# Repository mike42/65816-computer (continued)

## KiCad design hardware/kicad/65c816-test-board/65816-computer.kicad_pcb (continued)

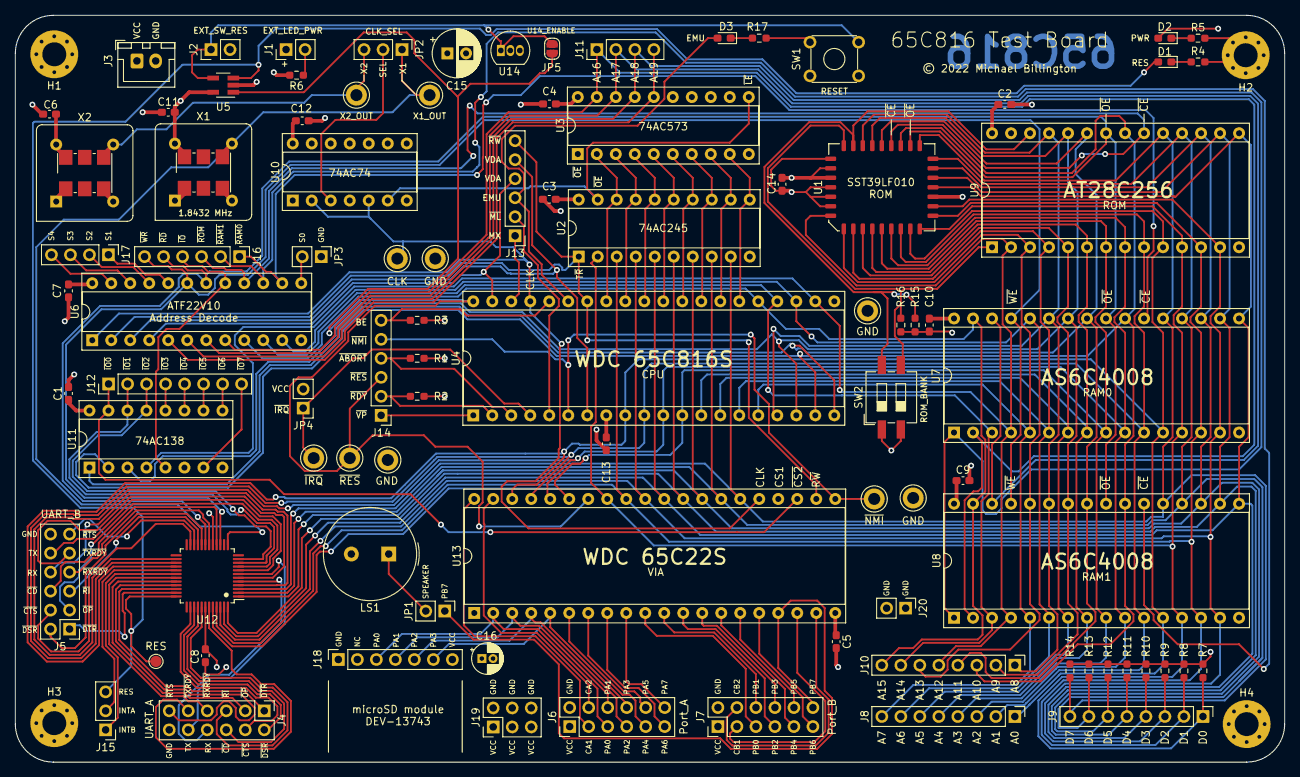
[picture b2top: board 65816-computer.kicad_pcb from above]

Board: 4 copper layers, 169.7 x 99.8 mm, 97 parts (0 on the bottom side), 128 nets.

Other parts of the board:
X1_ALT, X2_ALT: Oscillator_SMD_IDT_JU6-6_7.0x5.0mm_P2.54mm

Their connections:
+5V: X1_ALT.1, X1_ALT.6, X2_ALT.1, X2_ALT.6; also elsewhere on the board
/CPU& Bank Address Latching/CLK_UART: X1_ALT.4; also elsewhere on the board
GND: X1_ALT.3, X2_ALT.3; also elsewhere on the board
unnamed 127: X2_ALT.4; also elsewhere on the board

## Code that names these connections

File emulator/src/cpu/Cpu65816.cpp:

/*
 * This file is part of the 65816 Emulator Library.
 * Copyright (c) 2018 Francesco Rigoni.
 *
 * https://github.com/FrancescoRigoni/Lib65816
 *
 * This program is free software: you can redistribute it and/or modify
 * it under the terms of the GNU General Public License as published by
 * the Free Software Foundation, version 3.
 *
 * This program is distributed in the hope that it will be useful, but
 * WITHOUT ANY WARRANTY; without even the implied warranty of
 * MERCHANTABILITY or FITNESS FOR A PARTICULAR PURPOSE. See the GNU
 * General Public License for more details.
 *
 * You should have received a copy of the GNU General Public License
 * along with this program. If not, see <http://www.gnu.org/licenses/>.
 */

#include "Cpu65816.h"

#include <utility>

#ifdef EMU_65C02
#define LOG_TAG "Cpu65C02"
#else
#define LOG_TAG (mCpuStatus.emulationFlag() ? "Cpu6502" : "Cpu65816")
#endif

Cpu65816::Cpu65816(SystemBus &systemBus, std::shared_ptr<InterruptStatus> nmi, std::shared_ptr<InterruptStatus> irq) :
        mSystemBus(systemBus),
        mStack(&mSystemBus),
        nmi(nmi),
        irq(irq) {
    mPins.NMI = nmi->get();
}


void Cpu65816::setXL(uint8_t x) {
    mX = x;
}

void Cpu65816::setYL(uint8_t y) {
    mY = y;
}

void Cpu65816::setX(uint16_t x) {
    mX = x;
}

void Cpu65816::setY(uint16_t y) {
    mY = y;
}

void Cpu65816::setA(uint16_t a) {
    mA = a;
}

uint16_t Cpu65816::getA() {
    return mA;
}

Address Cpu65816::getProgramAddress() {
    return mProgramAddress;
}

Stack *Cpu65816::getStack() {
    return &mStack;
}

CpuStatus *Cpu65816::getCpuStatus() {
    return &mCpuStatus;
}


/**
 * Resets the cpu to its initial state.
 * */
void Cpu65816::reset() {
    setRESPin(true);
    mCpuStatus.setEmulationFlag();
    mCpuStatus.setAccumulatorWidthFlag();
    mCpuStatus.setIndexWidthFlag();
    mX &= 0xFF;
    mY &= 0xFF;
    mD = 0x0;
    mStack = Stack(&mSystemBus);
    mProgramAddress = Address(0x00, mSystemBus.readTwoBytes(Address(0x00, INTERRUPT_VECTOR_EMULATION_RESET)));
}

void Cpu65816::setRESPin(bool value) {
    if (value == false && mPins.RES == true) {
        reset();
    }
    mPins.RES = value;
}

void Cpu65816::setRDYPin(bool value) {
    mPins.RDY = value;
}

bool Cpu65816::executeNextInstruction() {
    if (mPins.RES) {
        return false;
    }
    if ((irq->get()) && (!mCpuStatus.interruptDisableFlag())) {
        /*
        The program bank register (PB, the A16-A23 part of the address bus) is pushed onto the hardware stack (65C816/65C802 only when operating in native mode).
        The most significant byte (MSB) of the program counter (PC) is pushed onto the stack.
        The least significant byte (LSB) of the program counter is pushed onto the stack.
        The status register (SR) is pushed onto the stack.
        The interrupt disable flag is set in the status register.
        PB is loaded with $00 (65C816/65C802 only when operating in native mode).
        PC is loaded from the relevant vector (see tables).
        */
        if (!mCpuStatus.emulationFlag()) {
            mStack.push8Bit(mProgramAddress.getBank());
            mStack.push16Bit(mProgramAddress.getOffset());
            mStack.push8Bit(mCpuStatus.getRegisterValue());
            mCpuStatus.setInterruptDisableFlag();
            mProgramAddress = Address(0x00, mSystemBus.readTwoBytes(Address(0x00, INTERRUPT_VECTOR_NATIVE_IRQ)));
        } else {
            mStack.push16Bit(mProgramAddress.getOffset());
            mStack.push8Bit(mCpuStatus.getRegisterValue());
            mCpuStatus.setInterruptDisableFlag();
            mProgramAddress = Address(0x00, mSystemBus.readTwoBytes(Address(0x00, INTERRUPT_VECTOR_EMULATION_BRK_IRQ)));
        }
    }
    // Edge detect NMI
    bool newNmi = nmi->get();
    if(!newNmi && mPins.NMI) {
        // De-activated
        mPins.NMI = false;
    } else if(newNmi && !mPins.NMI) {
        // Activated
        mPins.NMI = true;
        if (!mCpuStatus.emulationFlag()) {
            mStack.push8Bit(mProgramAddress.getBank());
            mStack.push16Bit(mProgramAddress.getOffset());
            mStack.push8Bit(mCpuStatus.getRegisterValue());
            mCpuStatus.setInterruptDisableFlag();
            mProgramAddress = Address(0x00, mSystemBus.readTwoBytes(Address(0x00, INTERRUPT_VECTOR_NATIVE_NMI)));
        } else {
            mStack.push16Bit(mProgramAddress.getOffset());
            mStack.push8Bit(mCpuStatus.getRegisterValue());
            mCpuStatus.setInterruptDisableFlag();
            mProgramAddress = Address(0x00, mSystemBus.readTwoBytes(Address(0x00, INTERRUPT_VECTOR_EMULATION_NMI)));
        }
    }
    // Fetch the instruction
    const uint8_t instruction = mSystemBus.readByte(mProgramAddress);
    OpCode opCode = OP_CODE_TABLE[instruction];
    // Execute it
    return opCode.execute(*this);
}

bool Cpu65816::accumulatorIs8BitWide() {
    // Accumulator is always 8 bit in emulation mode.
    if (mCpuStatus.emulationFlag()) return true;
        // Accumulator width set to one means 8 bit accumulator.
    else return mCpuStatus.accumulatorWidthFlag();
}

bool Cpu65816::accumulatorIs16BitWide() {
    return !accumulatorIs8BitWide();
}

bool Cpu65816::indexIs8BitWide() {
    // Index is always 8 bit in emulation mode.
    if (mCpuStatus.emulationFlag()) return true;
        // Index width set to one means 8 bit accumulator.
    else return mCpuStatus.indexWidthFlag();
}

bool Cpu65816::indexIs16BitWide() {
    return !indexIs8BitWide();
}

void Cpu65816::addToCycles(int cycles) {
    mTotalCyclesCounter += cycles;
    mSystemBus.clockTick(cycles);
}

void Cpu65816::subtractFromCycles(int cycles) {
    mTotalCyclesCounter -= cycles;
}

void Cpu65816::addToProgramAddress(int bytes) {
    mProgramAddress.incrementOffsetBy(bytes);
}

void Cpu65816::addToProgramAddressAndCycles(int bytes, int cycles) {
    addToCycles(cycles);
    addToProgramAddress(bytes);
}

uint16_t Cpu65816::indexWithXRegister() {
    return indexIs8BitWide() ? Binary::lower8BitsOf(mX) : mX;
}

uint16_t Cpu65816::indexWithYRegister() {
    return indexIs8BitWide() ? Binary::lower8BitsOf(mY) : mY;
}

void Cpu65816::setProgramAddress(const Address &address) {
    mProgramAddress = address;
}

uint64_t Cpu65816::getTotalCyclesCounter() const {
    return mTotalCyclesCounter;
}

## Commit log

2022-01-10 Initial commit, README only
2022-01-10 add address decode PLD definitions
2022-01-10 add ROM
2022-01-10 add KiCad project files for current design
2022-01-10 ignore generated PLD files
2022-01-10 ignore ca65 outputs
2022-01-22 upgrade project files to Kicad 6.0
2022-01-31 update computer, move test program to use native mode
2022-02-05 update example program to use native mode interrupts
2022-02-05 connect IRQ output of 65C22 to CPU NMI
2022-02-06 latest firmware, saves and restores same task (I think)
2022-02-07 fix bugs, formatting
2022-02-27 add extra 512 kB RAM, 74AC138 for future use
2022-03-02 update address decoding, extend README
2022-03-05 separate I/O schematic page, add SC16C752 for future use
2022-03-09 add FrancescoRigoni's lib65816 (GPLv3 and MIT logging library) to attempt emulator build
2022-03-09 consolidate emulator code into one CMakeLists
2022-03-09 rename .hpp -> .h, auto format all cpp code
2022-03-09 logs to stderr, remove include/ dir, further consolidation
2022-03-09 update all header/include guards
2022-03-09 start adding skeleton code for 8K ROM file loading
2022-03-10 bump to C++17, fix ROM loading, load reset vector from ROM on start - should really be requested from system bus when needed.
2022-03-11 qualify reads (for serial port)
2022-03-11 add blog post on multitasking
2022-03-14 add basic 65C22 VIA emulation for free-running timer; interrupt is not connected.
2022-03-14 add JetBrains project files to gitignore
2022-03-14 connect UART to circuit
2022-03-26 update emulation to improve interrupt handling
2022-03-26 switch off logging
2022-03-30 implement character I/O with curses instead (buffering issues)
2022-04-01 update ROM to UART test (does not work on real hardware)
2022-04-01 move all hardware files to hardware folder
2022-04-02 correct LICENSE, emulator is GPLv3
2022-04-02 update README for emulator
2022-04-11 update emulator to exit with contents of A register when STP is called
2022-04-11 remove curses, use plain non-canonical terminal input instead (avoids clearning the screen)
2022-04-11 update hardware files to match current WIP design
2022-04-11 update README with emulator blog post
2022-04-12 curses no longer required
2022-04-12 add software/ dir for test kernel
2022-04-12 split out interrupts
2022-04-16 add panic method to kernel
2022-04-18 fix/annotate suspected lib65816 bugs in 16-bit ADC and SBC
2022-04-19 add some test C functions, compiled to assembly and translated to ca65 syntax
2022-05-01 update schematic, add draft PCB
2022-05-07 pcb updates
2022-05-07 add gerbers for test board
2022-05-07 license firmware/hardware CC BY 4.0
2022-05-08 add build tool for ramdisk creation
2022-05-09 add mapping of ramdisk in emulator, work on interactive test program
2022-05-09 create empty directories during build - they aren't stored by git
2022-05-11 add backspace, Ctrl+U to shell
2022-05-15 break out ASCII codes, convert input parsing to state machine
2022-05-15 ignore up, down, left, right and similar input codes
2022-05-22 update ROM with simple POST routine
2022-05-22 update newer ROM test code
2022-06-04 add blog posts
2022-06-05 add 'hello world' translated from C.
2022-06-16 remove old test code from ROM
2022-06-16 wait until FIFO is empty before sending each char (slower).
2022-06-17 update ROM - WIP SD card testing.
2022-06-24 work towards SD card boot
2022-06-24 add option to run bootloader from SD card
2022-06-24 start testing access of ROM functions via software interrupt
2022-06-30 work on COP software interrrupt handler in ROM. it can now identify which method is being requested
2022-07-01 auto-format ROM source yay
2022-07-05 add bootloader placeholder
2022-07-05 move SD block read to software interrupt (COP) routine
2022-07-05 implement software interrupt (COP) routines for printing char, reading char, convert some ROM code to use this
2022-07-05 progress towards reading multiple blocks from software interrupt (COP) routine - most code commented
2022-07-12 work on SD boot, 3 attempts to reset card, allow loading multiple blocks of data through software interrupt
2022-07-17 update test programs - bootloader loading 8k kernel now but not to the address we would like to use.
2022-07-17 remove commented code, load placeholder kernel to $a000 for now
2022-07-19 start speeding up 512-byte SD card receive
2022-07-19 reduce stack and cpu flag operations further for SD card read
2022-07-19 remove some branching, move CPU mode flags outside of loop, make re-attempt of SD init more generic
2022-07-19 eliminate some more instructions to hopefully speed up SD card reads
2022-07-25 eliminate some more instructions from sd card block reads
2022-07-25 start upgrading hexdump code to use 65C816 features
2022-07-25 switch to far addressing in some places - a lot of this code does not work when DBR is not bank 0.
2022-08-07 first fix to hexdump outside of bank 0
2022-08-07 proper fix for hexdump code, start adding support for serial boot
2022-08-07 add rudimentary code to boot from serial via XMODEM transfer
2022-08-07 refine boot from serial
2022-08-07 update ROM routines to load data outside bank 0, update bootloader to load kernel to bank 1
2022-08-07 update bootloader to load 128k of the ramdisk (hopefully)
2022-08-08 fixed memory map in hardware, UART is now at correct memory location
2022-08-13 update XCE instruction in emulator
    found that switching from native mode to emulation moe does not switch index and accumulator width to 16-bit on real CPU
2022-08-13 update emulated VIA to return its startup default for interrupt enable register (IER)
2022-08-13 indicate that emulated UART always ready / has empty TX register
2022-08-13 update emulator software interrupt handling
    COP instruction was setting program counter to $ffe4, should read address at $ffe4 and set program counter to that value instead.
2022-08-13 fix emulator bug: JSR absolute indexed by X should not push bank byte to stack.
2022-08-25 TerminalWrapper to use unix socket instead of stdio
2022-08-28 update emulator to remove bugs with characters 0x00 and > 0x7f, also attempt to slow it down to match speed of hardware
2022-09-03 Add blog post
2022-09-17 add make target for writing ROM to SST39LF010 flash chip
2022-09-23 add new blog entry
2022-10-15 reorganise hardware folder to allow multiple PCB's
2022-10-15 add i2c breakout board
2023-01-08 update bootloader code (not using ramdisk)
2023-01-08 placeholder for snake game
2023-03-04 Add new blog post
2023-03-29 start manually compiling snake game
2023-03-29 progress on porting snake. mainly notes at this stage
2023-03-30 snake game attempt: notes from more troubleshooting
2023-05-03 split emulator into library and main binary to allow testing
2023-05-03 add google test to emulator, blank placeholder test for now
2023-05-03 work towards running tests from emulator, more to come
2023-05-03 add example unit test project, locate .lbl file for binary output (not parsing yet)
2023-05-04 add parsing of VICE label files to emulator
2023-05-04 fix debug label file parsing, add fuzzer and update emulator README
2023-05-05 add alternative ROM build for emulator use
2023-05-05 add --trace option to emulator, to print every CPU instruction being executed
2023-05-05 replace trace output, now includes label names when program counter hits them
2023-05-05 fix handling of higher banks of RAM
2023-05-05 switch test program to print "Hello, world!" instead of "z".
2023-05-05 work on welcome screen for snake demo - have discovered only first 512 bytes are loading correctly from SD card
2023-05-06 add test program which hexdumps full 8KiB of program loaded from SD - definitely not loading correctly
2023-05-06 add WIP snake game demo
2023-05-06 ah there's your problem - was reading in same block instead of new blocks
2023-05-13 add github actions (demo)
2023-06-12 add a test
2023-06-13 add automated build
    this adds an initial Dockerfile defining build dependencies, a build.sh to define steps, and GitHub action to run the script each change.
    some of the trickier stuff (eg. PLD file generation) is not included at this stage.
2023-06-13 Update README.md
    Build status badge
2023-06-17 fix emulator bugs with xce resetting stack unnecessarily, and test hanging when 'brk' is triggered (will now fail test)
    in-progress random number functions are now in standalone file so they can be tested
2023-06-17 implement Xorshift, add test
2023-06-19 isolate tests a bit better, add new ERROR label for when the breakpoint at $0000 fires
2024-06-29 mkae compatible with newer libboost version
